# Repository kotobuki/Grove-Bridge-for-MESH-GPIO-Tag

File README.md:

# Grove Bridge for MESH GPIO Tag

A bridge between the [**MESH GPIO Tag**](https://meshprj.com/en/tag/MESH-100GP-GPIO.html) by Sony and the [**Grove**](http://www.seeedstudio.com/wiki/Category:Grove) family by Seeed Studio.

## Bill of Materials

|Part/Designator|Manufacture Part Number/Seeed SKU|Quantity|
|---------------|---------------------------------|--------|
|PCB||1|
|J1,J2,J3,J4|Seeed SKU: [320110033](http://www.seeedstudio.com/depot/index.php?main_page=opl_info&opl_id=4)|4|
|JP1|Digi-Key: [S2011EC-05-ND](http://www.digikey.jp/product-search/ja?keywords=S2011EC-05-ND)|1|

## How to 'compile'?

Place an order at the [Fusion PCBA prototype](http://www.seeedstudio.com/service/index.php?r=pcb) service.

## Compatible Modules

* Sensors
  * [Grove - Switch(P)](http://www.seeedstudio.com/wiki/Grove_-_Switch(P))
  * [Grove - Rotary Angle Sensor](http://www.seeedstudio.com/wiki/Grove_-_Rotary_Angle_Sensor)
  * [Grove - Slide Potentiometer](http://www.seeedstudio.com/wiki/Grove_-_Slide_Potentiometer)
  * [Grove - Touch Sensor](http://www.seeedstudio.com/wiki/Grove_-_Touch_Sensor)
  * [Grove - Light Sensor](http://www.seeedstudio.com/wiki/Grove_-_Light_Sensor)
  * [Grove - Single Axis Analog Gyro](http://www.seeedstudio.com/wiki/Grove_-_Single_Axis_Analog_Gyro)
* Actuators
  * [Grove - LED Socket Kit](http://www.seeedstudio.com/wiki/Grove_-_LED)
  * [Grove - Buzzer](http://www.seeedstudio.com/wiki/Grove_-_Buzzer)
  * [Grove - Vibration Motor](http://www.seeedstudio.com/wiki/Grove_-_Vibration_Motor)

## Incompatible Modules

* [Grove - Button](http://www.seeedstudio.com/wiki/Grove_-_Button) (as a digital input device, can be used as an analog input device)
* [Grove - Servo](http://www.seeedstudio.com/wiki/Grove_-_Servo)

# License Information

This design document is licensed by Shigeru Kobayashi under the terms of the [Creative Commons Attribution-ShareAlike 4.0 International Public License](http://creativecommons.org/licenses/by-sa/4.0/).

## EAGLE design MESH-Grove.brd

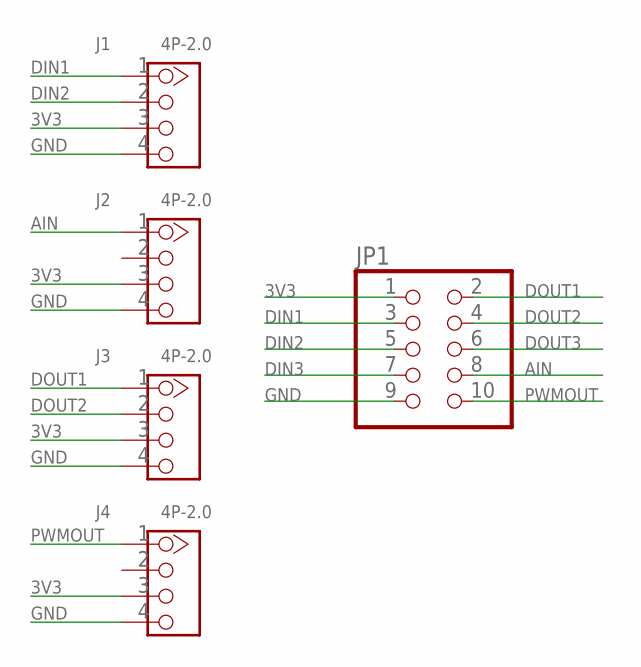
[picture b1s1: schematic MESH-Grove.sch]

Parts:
J1, J2, J3, J4: 4P-2.0; HW4-2.0
JP1: PINHD-2X5; 2X05

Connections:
3V3: J1.3, J2.3, J3.3, J4.3, JP1.1
AIN: J2.1, JP1.8
DIN1: J1.1, JP1.3
DIN2: J1.2, JP1.5
DIN3: JP1.7
DOUT1: J3.1, JP1.2
DOUT2: J3.2, JP1.4
DOUT3: JP1.6
GND: J1.4, J2.4, J3.4, J4.4, JP1.9
PWMOUT: J4.1, JP1.10

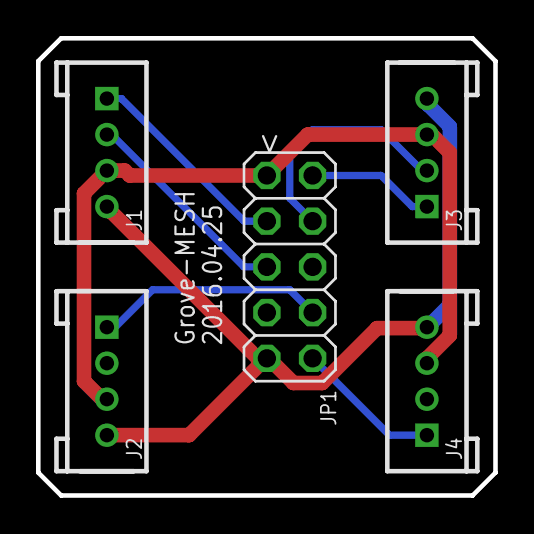
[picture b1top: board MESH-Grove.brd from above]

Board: 2 copper layers, 25.4 x 25.4 mm, 5 parts (0 on the bottom side), 8 nets.

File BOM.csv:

Part/Designator,Manufacture Part Number/Seeed SKU,Quantity"J1,J2,J3,J4",320110033,4JP1,PRPC005DAAN-RC,1

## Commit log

2016-04-25 Initial version
2016-04-25 Add the licence
2016-04-26 Add an image of MESH-Grove
2016-04-26 Fix the link of the image
2016-04-26 Update the image of the MESH-Grove
2016-04-26 Update the BOM list and the compatible modules and
2016-04-27 Add a module to the compatible modules list
2016-04-27 Update the part number for JP1
2016-04-28 Replace the Digi-Key part number of JP1 with the manufacture part number
2016-04-28 Moved the silk for Grove connectors a little bit
2016-05-01 Change the name
    Change the name to avoid confusion with official products by the MESH
    project
2016-05-01 Revert "Change the name"
    This reverts commit f9e46613978591442f2dbf96a1cbcc250044e6b9.
